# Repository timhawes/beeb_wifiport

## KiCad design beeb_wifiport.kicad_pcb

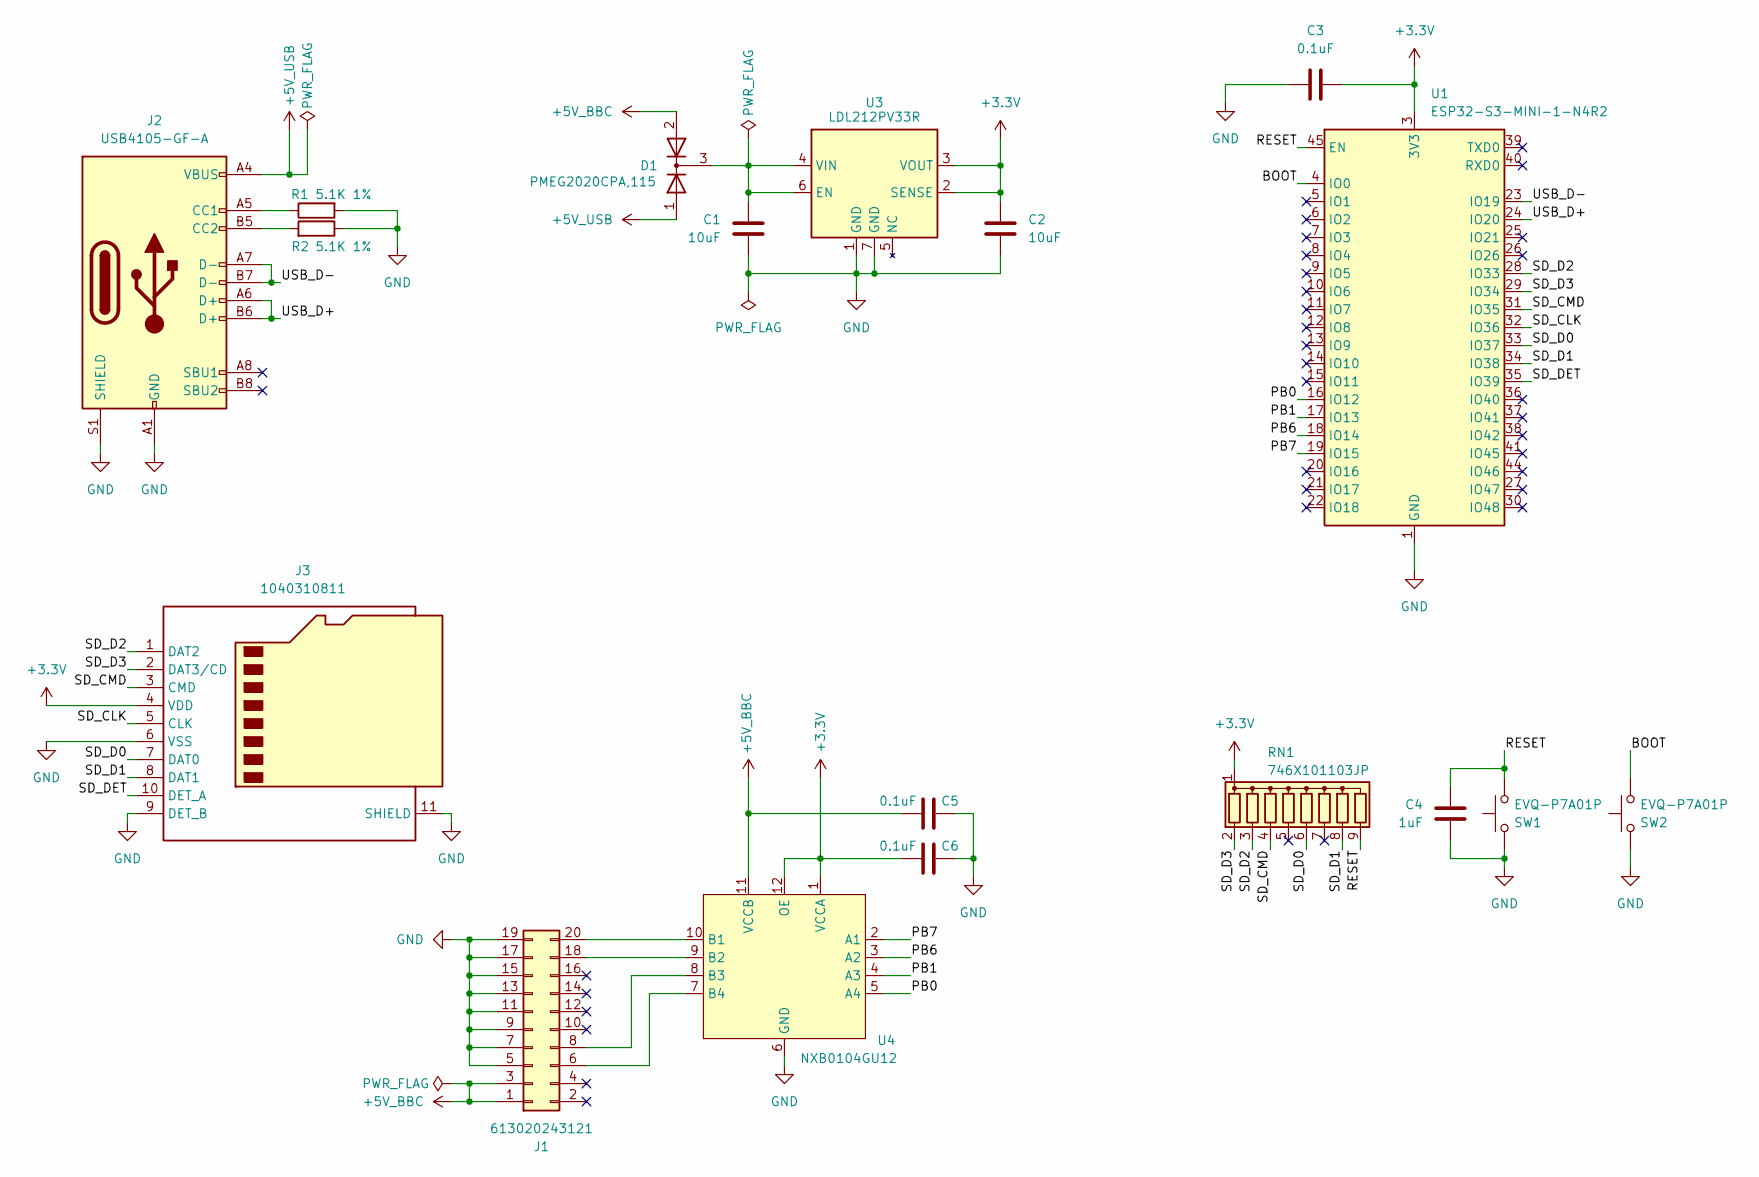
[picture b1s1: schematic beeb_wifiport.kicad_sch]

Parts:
C1, C2: 10uF; C_0603_1608Metric
C3, C5, C6: 0.1uF; C_0402_1005Metric
C4: 1uF; C_0402_1005Metric
D1: PMEG2020CPA,115; HUSON-3-1EP_2x2mm_P1.3mm_EP1.1x1.6mm
J1: 613020243121; PinSocket_2x10_P2.54mm_Horizontal
J2: USB4105-GF-A; USB_C_Receptacle_GCT_USB4105-xx-A_16P_TopMnt_Horizontal
J3: 1040310811; microSD_HC_Molex_104031-0811
R1, R2: 5.1K 1%; R_0402_1005Metric
RN1: 746X101103JP; CTS_746X101103JP
SW1, SW2: EVQ-P7A01P; SW_SPST_EVQP7A
U1: ESP32-S3-MINI-1-N4R2; ESP32-S2-MINI-1
U3: LDL212PV33R; DFN-6-1EP_2x2mm_P0.5mm_EP1.02x1.6mm
U4: NXB0104GU12; NXP_XQFN12_SOT1174-1

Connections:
+3.3V: C2.1, C3.2, C6.2, J3.4 (VDD), RN1.1 (common), U1.3 (3V3), U3.2 (SENSE), U3.3 (VOUT), U4.1 (VCCA), U4.12 (OE)
+5V_BBC: C5.2, D1.2 (A), J1.1, J1.3, U4.11 (VCCB)
+5V_USB: D1.1 (A), J2.A4 (VBUS), J2.A9 (VBUS), J2.B4 (VBUS), J2.B9 (VBUS)
/BOOT: SW2.1, U1.4 (IO0)
/PB0: U1.16 (IO12), U4.5 (A4)
/PB1: U1.17 (IO13), U4.4 (A3)
/PB6: U1.18 (IO14), U4.3 (A2)
/PB7: U1.19 (IO15), U4.2 (A1)
/RESET: C4.1, RN1.9 (R8), SW1.1, U1.45 (EN)
/SD_CLK: J3.5 (CLK), U1.32 (IO36)
/SD_CMD: J3.3 (CMD), RN1.4 (R3), U1.31 (IO35)
/SD_D0: J3.7 (DAT0), RN1.6 (R5), U1.33 (IO37)
/SD_D1: J3.8 (DAT1), RN1.8 (R7), U1.34 (IO38)
/SD_D2: J3.1 (DAT2), RN1.3 (R2), U1.28 (IO33)
/SD_D3: J3.2 (DAT3/CD), RN1.2 (R1), U1.29 (IO34)
/SD_DET: J3.10 (DET_A), U1.35 (IO39)
/USB_D+: J2.A6 (D+), J2.B6 (D+), U1.24 (IO20)
/USB_D-: J2.A7 (D-), J2.B7 (D-), U1.23 (IO19)
GND: C1.2, C2.2, C3.1, C4.2, C5.1, C6.1, J1.5, J1.7, J1.9, J1.11, J1.13, J1.15, J1.17, J1.19, J2.A1 (GND), J2.A12 (GND), J2.B1 (GND), J2.B12 (GND), J2.S1 (SHIELD), J3.6 (VSS), J3.9 (DET_B), J3.11 (SHIELD), R1.2, R2.1, SW1.2, SW2.2, U1.1 (GND), U1.2 (GND), U1.42 (GND), U1.43 (GND), U1.46 (GND), U1.47 (GND), U1.48 (GND), U1.49 (GND), U1.50 (GND), U1.51 (GND), U1.52 (GND), U1.53 (GND), U1.54 (GND), U1.55 (GND), U1.56 (GND), U1.57 (GND), U1.58 (GND), U1.59 (GND), U1.60 (GND), U1.61 (GND), U1.62 (GND), U1.63 (GND), U1.64 (GND), U1.65 (GND), U3.1 (GND), U3.7 (GND), U4.6 (GND)
unnamed: C1.1, D1.3 (K), U3.4 (VIN), U3.6 (EN)
unnamed: J1.6, U4.7 (B4)
unnamed: J1.8, U4.8 (B3)
unnamed: J1.18, U4.9 (B2)
unnamed: J1.20, U4.10 (B1)
unnamed: J2.A5 (CC1), R1.1
unnamed: J2.B5 (CC2), R2.2

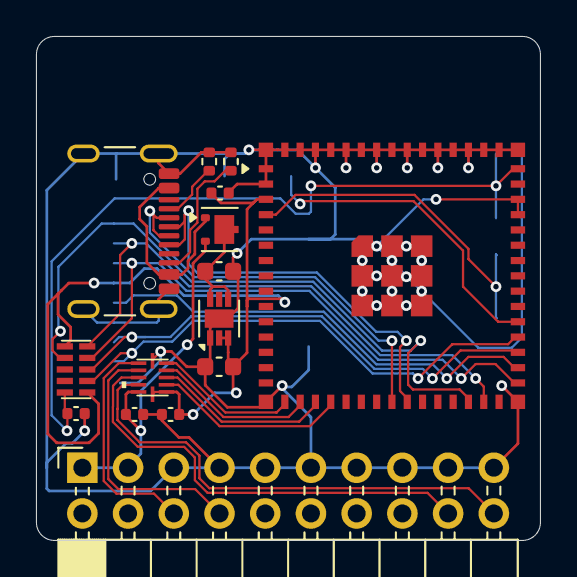
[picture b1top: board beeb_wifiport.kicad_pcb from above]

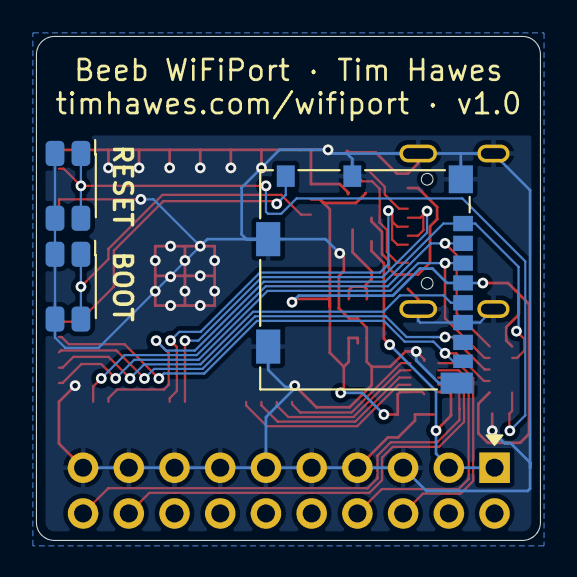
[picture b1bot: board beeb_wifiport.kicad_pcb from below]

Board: 2 copper layers, 28.0 x 28.0 mm, 18 parts (3 on the bottom side), 26 nets.

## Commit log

2024-07-26 Interactive BOM
2024-07-26 Clarify part numbers
